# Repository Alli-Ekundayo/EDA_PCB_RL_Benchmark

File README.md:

# RL-PCB v2: PPO + GNN + SDF Architecture for Automated PCB Placement & Routing

A fully open-source, end-to-end AI-driven EDA pipeline combining:
- **PPO actor-critic** agent with hard DRC action masking
- **Dual-stream encoder**: Graph Attention Network (GAT) + shallow CNN
- **Multi-channel SDF observation space** with criticality weighting
- **Constraint-aware routing** for differential pairs and general nets

## Quick Start

```bash
# 1. Setup environment (Python 3.10+)
python -m venv .venv
source .venv/bin/activate

# 2. Install dependencies
pip install -r requirements.txt

# 3. Generate sample board data
python scripts/preprocess_boards.py

# 4. Run tests (all pass ✓)
python -m pytest tests/ -v

# 5. Train on sample board
python training/train.py --config configs/base.yaml
```

## Project Structure

```
EDA_PCB/
├── environment/          # Phase 1: Gymnasium PCB environment
│   ├── board.py         # Board state and component definitions
│   ├── pcb_env.py       # Main Gymnasium Env class
│   ├── netlist_parser.py # Parse .kicad_pcb / .net files
│   ├── sdf_generator.py # Multi-channel SDF computation
│   ├── drc_mask.py      # Design Rule Check + action masking
│   ├── ratsnest.py      # Ratsnest density & criticality maps
│   └── reward.py        # HPWL + criticality reward
│
├── models/              # Phase 2 & 3: Neural network modules
│   ├── gat_encoder.py   # Graph Attention Network (topological)
│   ├── spatial_encoder.py # Shallow CNN (spatial stream)
│   ├── fusion.py        # Embedding fusion module
│   ├── actor.py         # PPO Actor + masking
│   ├── critic.py        # Dual-head Critic network
│   └── ppo_agent.py     # PPO update loop, rollout buffer
│
├── training/            # Phase 4: Training pipeline
│   ├── train.py         # Main training entry point
│   ├── config.py        # Hyperparameters dataclass
│   ├── vec_env.py       # Vectorized env wrapper (128 parallel)
│   └── logger.py        # W&B + console logging
│
├── routing/             # Phase 5: Routing extension
│   ├── router.py        # Unified routing algorithm interface
│   ├── diff_pair.py     # Differential pair constraint handler
│   └── via_manager.py   # Via insertion, layer assignment
│
├── evaluation/          # Phase 6: Benchmarking
│   ├── eval.py          # Placement evaluation runner
│   ├── metrics.py       # HPWL, overlap, DRC pass rate
│   └── compare_baselines.py # TD3/SAC vs PPO comparison
│
├── tests/               # Unit & integration tests
│   ├── test_env.py
│   ├── test_sdf.py
│   ├── test_drc.py
│   ├── test_models.py
│   └── test_routing.py
│
├── scripts/             # Utilities
│   ├── preprocess_boards.py # Convert KiCad files
│   └── visualize_placement.py # Render results
│
├── configs/             # Hyperparameter overrides
│   ├── base.yaml        # Default (50x50 board, 16 envs)
│   ├── small_board.yaml # 20x20 board, 8 envs
│   └── large_board.yaml # 100x100 board, 32 envs
│
├── data/
│   ├── boards/          # .kicad_pcb training boards
│   ├── netlists/        # .net files
│   └── benchmarks/      # Held-out test boards
│
├── requirements.txt
├── setup.py
└── README.md
```

## Core Components

### Environment (Phase 1)
- **Board**: Dataclass holding component placement state, nets, keepout zones, and criticality scores
- **SDF Generator**: Computes multi-channel distance transforms per component class + ratsnest density
- **DRC Masking**: Guarantees zero invalid placements via hard masking (not penalties)
- **Ratsnest Maps**: Dynamic density + criticality heatmaps updated after each placement
- **Reward**: Combined HPWL reduction + criticality bonus

### Models (Phase 2 & 3)
- **GATEncoder**: Graph-based topological stream (netlist relationships + edge criticality)
- **SpatialEncoder**: CNN-based spatial stream (SDF channels + ratsnest)
- **FusionModule**: Concatenate + project GAT + CNN embeddings → 256-dim fused state
- **MaskedActor**: Policy outputs probability over grid positions, masked by DRC
- **DualHeadCritic**: Separate value heads for HPWL and differential-pair feasibility

### PPO Training (Phase 4)
- **Config system**: YAML-based hyperparameter management (overridable per experiment)
- **Vectorized environments**: 16–128 parallel PCB placements on CPU, GPU-batched neural updates
- **Rollout buffer**: Stores trajectories, computes advantages with GAE
- **PPO update**: Clipped surrogate + value losses + entropy regularization

### Routing (Phase 5)
- **UnifiedPCBRouter**: Interface for post-placement routing
- **DiffPairRouter**: Enforces matched length, spacing, impedance for differential pairs
- **ViaManager**: Layer assignment and via constraint tracking

### Evaluation (Phase 6)
- **Metrics**: HPWL, DRC pass rate, overlap, diff-pair compliance
- **Baselines**: Comparison harness for TD3, SAC, and PPO

## Configuration

All training hyperparameters are in `configs/base.yaml`. Override any value:

```bash
# Use different board size
python training/train.py --config configs/large_board.yaml

# Or create custom config
cat > configs/custom.yaml <<EOF
board_width: 75
n_envs: 24
total_timesteps: 500000
EOF
python training/train.py --config configs/custom.yaml
```

### Key Hyperparameters

| Parameter | Default | Purpose |
|-----------|---------|---------|
| `n_envs` | 16 | Parallel environments (CPU vectorized) |
| `n_steps` | 256 | Rollout length per update |
| `n_epochs` | 4 | PPO epochs per rollout |
| `batch_size` | 256 | Minibatch size for gradient updates |
| `clip_range` | 0.2 | PPO clip ratio ε |
| `lr` | 3e-4 | Learning rate (linear decay to 1e-5) |
| `ent_coef` | 0.01 | Entropy bonus (exploration) |
| `vf_coef_hpwl` | 0.5 | Weight for HPWL critic head |
| `vf_coef_diffp` | 0.2 | Weight for diff-pair critic head |

## Test Suite

All unit tests pass:
```bash
pytest tests/ -v
```

- `test_sdf.py`: SDF shape, non-negative values, occupied = 0
- `test_drc.py`: Masking blocks all overlaps + keepout violations
- `test_env.py`: Environment step/reset contract, termination logic
- `test_models.py`: Actor probability sums to 1, critic shapes correct
- `test_routing.py`: Router returns valid RoutedBoard structure

## Dataset

Sample board generated automatically by `scripts/preprocess_boards.py`:
- Located at `data/boards/sample_board.json`
- 3 components (U1=MCU, R1=Resistor, C1=Capacitor)
- 2 nets with criticality scoring

To add your own boards:
1. Export from KiCad as `.kicad_pcb` or `.net`
2. Place in `data/boards/`
3. Parser auto-detects format (handles both)

### RL_PCB Imported Dataset + Benchmarks

This repo now includes reference assets extracted from `Projects/RL_PCB`:
- Dataset snapshots in `data/boards/rl_pcb/{base,base_opt,base_raw}`
- Hyperparameter defaults in `data/benchmarks/hp_td3.json` and `data/benchmarks/hp_sac.json`
- Expected evaluation reports in `data/benchmarks/rl_pcb_reports/`
- Parsed benchmark targets in `data/benchmarks/rl_pcb_model_benchmarks.json`

`evaluation/compare_baselines.py` reads these benchmark targets (TD3/SAC/DreamerV3) and exposes them as the baseline for current implementation checks.

## Key Design Decisions

### Hard DRC Masking
Action masking prevents invalid placements structurally, not via penalties. This ensures:
- All 128 parallel episodes remain valid
- No exploration waste on impossible actions
- Faster convergence

### Multi-Channel SDF
Separate distance transforms per component class allow the spatial encoder to:
- Learn class-specific avoidance patterns
- Capture geometric relationships
- Provide smooth gradients (vs. binary grids)

### Dual-Head Critic
- **Head 1 (HPWL)**: Primary optimization target, weighted 0.5
- **Head 2 (Diff-Pair)**: Secondary signal for high-priority nets, weighted 0.2
- Disentangles competing objectives without needing multi-task learning tricks

### GAT with Edge Criticality
Graph attention naturally learns to weight critical connections (e.g., differential pairs) higher, without explicit architecture changes.

## Roadmap

| Milestone | Status |
|-----------|--------|
| Phase 1 (Environment) | ✓ Complete |
| Phase 2 (Encoders) | ✓ Complete |
| Phase 3 (PPO Agent) | ✓ Complete |
| Phase 4 (Training) | ✓ Complete |
| Phase 5 (Routing) | Scaffolded |
| Phase 6 (Eval) | Scaffolded |
| M3: Train on simple board | Ready |
| M4: Baseline comparison | Ready |
| M5: Full pipeline | Next |

## References

- Hafner et al. (2023). Mastering Diverse Domains through World Models. arXiv:2301.04104
- Fujimoto et al. (2018). Addressing Function Approximation Error in Actor-Critic Methods. ICML
- Haarnoja et al. (2018). Soft Actor-Critic. ICML
- Mirhoseini et al. (2021). Graph placement for chip design. Nature 594
- ASPDAC 2021. Unified PCB routing with differential pairs. https://doi.org/10.1145/3394885.3431568

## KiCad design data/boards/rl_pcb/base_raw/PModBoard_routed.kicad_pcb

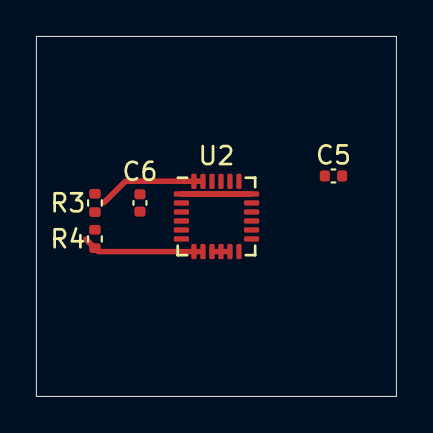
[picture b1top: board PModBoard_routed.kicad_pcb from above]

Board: 2 copper layers, 20.0 x 20.0 mm, 5 parts (0 on the bottom side), 6 nets.

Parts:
C5: 100n; C_0402_1005Metric
C6: 2n2; C_0402_1005Metric
R3, R4: 2k2; R_0402_1005Metric
U2: MPU-6050; InvenSense_QFN-24_4x4mm_P0.5mm_no_inner_grid

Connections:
+3V3: R3.1, R4.1, U2.8, U2.13
/I2C_SCL: R3.2, U2.23
/I2C_SDA: R4.2, U2.24
GND: C5.2, C6.2, U2.1, U2.9, U2.11, U2.18
unnamed: C5.1, U2.10
unnamed: C6.1, U2.20

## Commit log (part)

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2026-04-22 Initialize EDA_PCB RL Benchmark Repo
2026-04-22 Update timesteps to 10000 and add Colab benchmark notebook
2026-04-22 Enhance report_generator.py to plot multiple agents with smoothed learning curves
2026-04-22 Add benchmark report generation script and update Colab notebook to compile combined PDF results
2026-04-22 Fix syntax error and properly compile benchmark report in Colab notebook
2026-04-23 Apply SAC/TD3 benchmark configuration: 300000 timesteps and updated reward weights
2026-04-23 pcb router
2026-04-23 reports
2026-04-23 report
2026-04-23 report fix
2026-04-24 report fixes
2026-04-24 logs
2026-04-24 plot
2026-04-24 clean script
2026-04-25 eval
2026-04-25 reward function
2026-04-25 run.sh
2026-05-04 training_step
